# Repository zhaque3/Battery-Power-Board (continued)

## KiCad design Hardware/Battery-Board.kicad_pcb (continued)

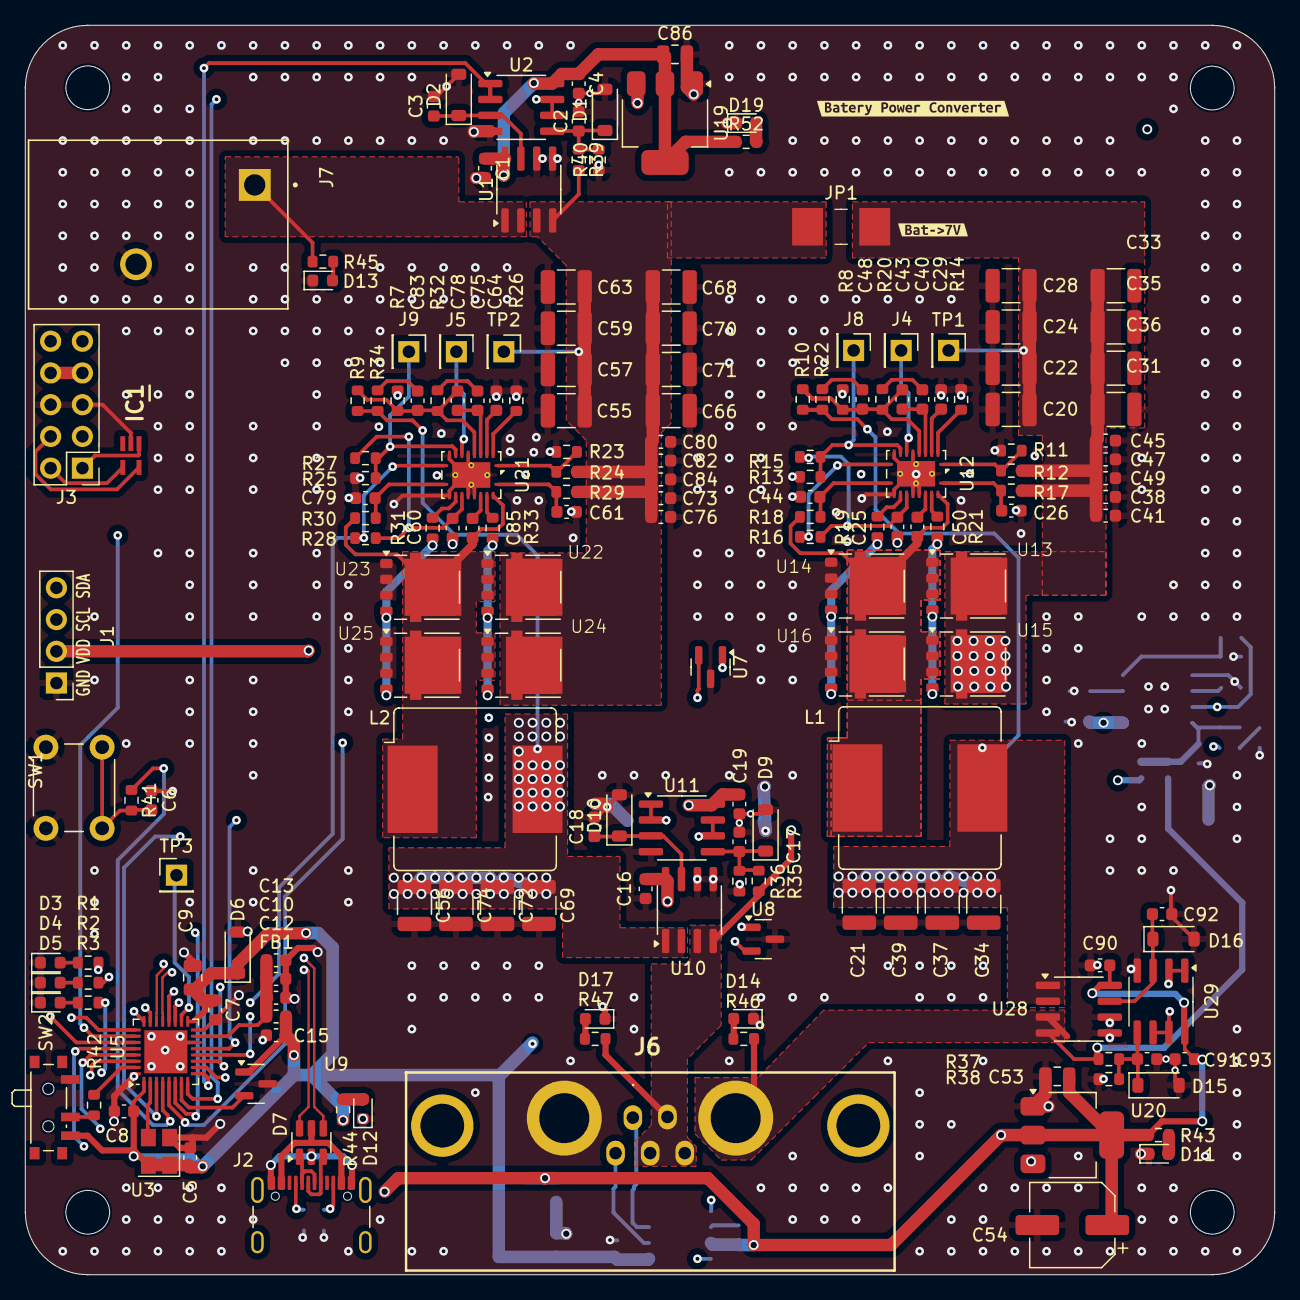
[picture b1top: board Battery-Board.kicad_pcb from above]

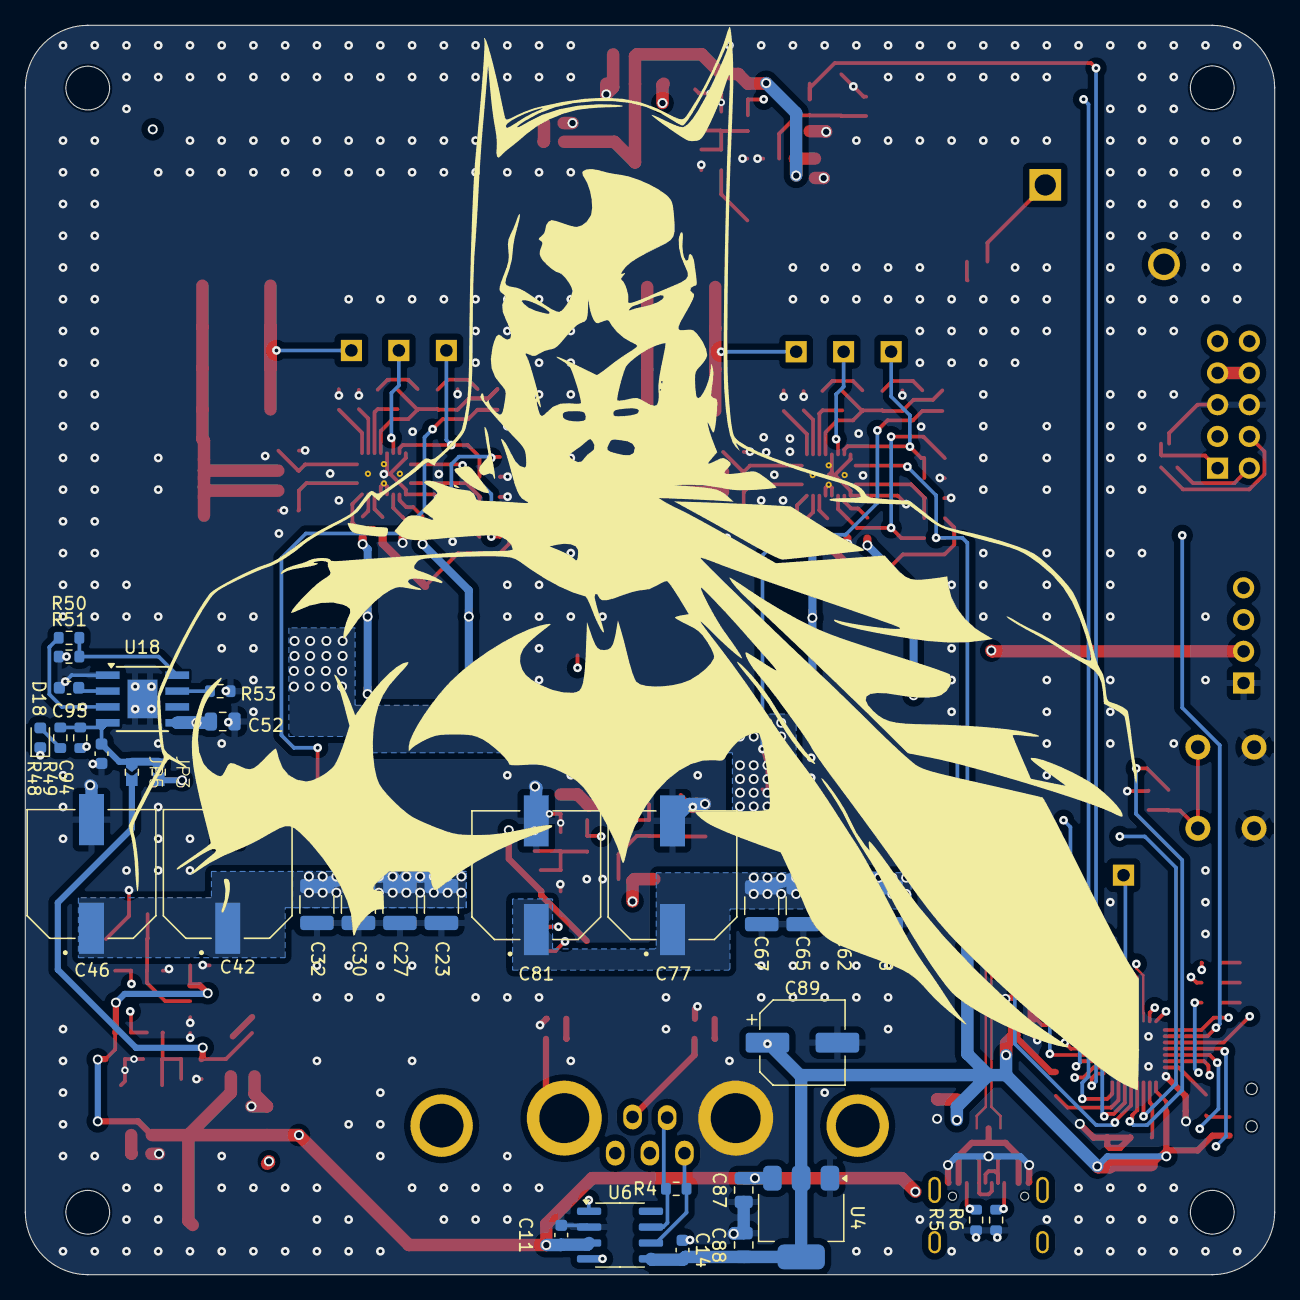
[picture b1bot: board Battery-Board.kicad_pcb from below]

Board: 4 copper layers, 100.0 x 100.0 mm, 220 parts (36 on the bottom side), 104 nets.

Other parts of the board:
C64: 47n; C_0603_1608Metric
C75: 5600pF; C_0603_1608Metric
C78: 150pF; C_0603_1608Metric
C79: 15pF; C_0603_1608Metric
C83: 1800pF; C_0603_1608Metric
R23: 18.2k; R_0603_1608Metric
R24: 250k; R_0603_1608Metric
R26: 46.4k; R_0603_1608Metric
R29: 2.2; R_0603_1608Metric
R30: 680R; R_0603_1608Metric
R34: 1k; R_0603_1608Metric
R50: 23k7; R_0603_1608Metric
kibuzzard-6785F55D: G***; kibuzzard-6785F55D
kibuzzard-67848C10: G***; kibuzzard-67848C10
kibuzzard-67848C36: G***; kibuzzard-67848C36

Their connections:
/DC-DC-Converters/DC-DC-Buck-Converter2/FB: C78.2, C83.1; also elsewhere on the board
/DC-DC-Converters/DC-DC-Buck-Converter2/Output: R34.2; also elsewhere on the board
/DC-DC-Converters/DC-DC-Buck-Converter2/POWER_IN: R24.1, R29.1; also elsewhere on the board
GND: C64.1, C79.1, R23.1, R26.2; also elsewhere on the board
unnamed 55: C75.2; also elsewhere on the board
unnamed: C83.2, R34.1
unnamed 90: R50.1; also elsewhere on the board
unnamed 92: R50.2; also elsewhere on the board
unnamed 95: C75.1, C78.1; also elsewhere on the board
unnamed 96: R23.2, R24.2; also elsewhere on the board
unnamed 98: C79.2, R30.1; also elsewhere on the board
unnamed 100: R26.1; also elsewhere on the board
unnamed 101: C64.2; also elsewhere on the board
unnamed 102: R30.2; also elsewhere on the board
unnamed 104: R29.2; also elsewhere on the board

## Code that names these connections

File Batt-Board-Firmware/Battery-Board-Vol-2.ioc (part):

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Mcu.Name=STM32G491K(C-E)Ux
Mcu.Package=UFQFPN32
Mcu.UserName=STM32G491KEUx
PA0.GPIOParameters=GPIO_Label
PA0.GPIO_Label=BUCK_TEMP_SENSE
PA0.Mode=IN1-Single-Ended
PA0.Signal=ADC1_IN1
PA1.GPIOParameters=GPIO_Label
PA1.GPIO_Label=OP_TEMP_SENSE
PA1.Mode=IN2-Single-Ended
PA1.Signal=ADC1_IN2
PA10.GPIOParameters=GPIO_Label
PA10.GPIO_Label=GPLED2
PA10.Signal=GPIO_Output
PA11.Mode=Device
PA11.Signal=USB_DM
PA12.Mode=Device
PA12.Signal=USB_DP
PA13.Mode=Serial_Wire
PA13.Signal=SYS_JTMS-SWDIO
PA14.Mode=Serial_Wire
PA14.Signal=SYS_JTCK-SWCLK
PA15.Mode=I2C
PA15.Signal=I2C1_SCL
PA2.GPIOParameters=GPIO_Label
PA2.GPIO_Label=CNTLR_TEMP_SENSE
PA2.Mode=IN3-Single-Ended
PA2.Signal=ADC1_IN3
PA3.GPIOParameters=GPIO_Label
PA3.GPIO_Label=VMON_IN
PA3.Mode=IN4-Single-Ended
PA3.Signal=ADC1_IN4
PA4.GPIOParameters=GPIO_Label
PA4.GPIO_Label=IMON_IN
PA4.Mode=IN17-Single-Ended
PA4.Signal=ADC2_IN17
PA5.GPIOParameters=GPIO_Label
PA5.GPIO_Label=GPLED3
PA5.Signal=GPIO_Output
PA6.GPIOParameters=GPIO_Label
PA6.GPIO_Label=IMON_7V
PA6.Mode=IN3-Single-Ended
PA6.Signal=ADC2_IN3
PA7.GPIOParameters=GPIO_Label
PA7.GPIO_Label=VMON_7V
PA7.Mode=IN4-Single-Ended
PA7.Signal=ADC2_IN4
PA8.Mode=Clock-out
PA8.Signal=RCC_MCO
PA9.GPIOParameters=GPIO_Label
PA9.GPIO_Label=GPLED1
PA9.Signal=GPIO_Output
PB0.GPIOParameters=GPIO_Label
PB0.GPIO_Label=IMON_12V
PB0.Mode=IN15-Single-Ended
PB0.Signal=ADC1_IN15
PB3.GPIOParameters=GPIO_Label
PB3.GPIO_Label=PG_7V
PB3.Signal=GPIO_Input
PB4.GPIOParameters=GPIO_Label
PB4.GPIO_Label=PG_12V
PB4.Signal=GPIO_Input
PB5.GPIOParameters=GPIO_PuPd
PB5.GPIO_PuPd=GPIO_PULLUP
PB5.Mode=FDCAN_Activate
PB5.Signal=FDCAN2_RX
PB6.Mode=FDCAN_Activate
PB6.Signal=FDCAN2_TX
PB7.Mode=I2C
PB7.Signal=I2C1_SDA
PF0-OSC_IN.Mode=HSE-External-Clock-Source
PF0-OSC_IN.Signal=RCC_OSC_IN
PF1-OSC_OUT.GPIOParameters=GPIO_Label
PF1-OSC_OUT.GPIO_Label=VMON_12V
PF1-OSC_OUT.Mode=IN10-Single-Ended
PF1-OSC_OUT.Signal=ADC2_IN10
RCC.HSE_VALUE=8000000
RCC.SYSCLKFreq_VALUE=170000000
RCC.SYSCLKSource=RCC_SYSCLKSOURCE_PLLCLK
board=custom

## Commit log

2025-12-18 update
    Updated formatting and improved clarity in the README.
